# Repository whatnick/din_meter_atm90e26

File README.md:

# DIN Rail / PCI-X1 compatible ATM90E26 Metering Module

This is a 2 unit DIN-Rail size in width ATM90E26 based metering module with a host of nice features, designed for use with the DIN-Rail energy monitor modules system.

## Features

- PCI-X1 lower connector for interface with power and analog voltage/current signals.
- x2 ATM90E26 energy monitor ASICs and associated crystals, RC filter networks.
- Molex SPI bus and power pass-through upper connector.
- Dense single-sided PCB with 0402 passives.
- Test points and jumpers on the bottom to allow additional uses.

## Renders

**DIN Meter ATM90E26 Front**

**DIN Meter ATM90E26 Back**

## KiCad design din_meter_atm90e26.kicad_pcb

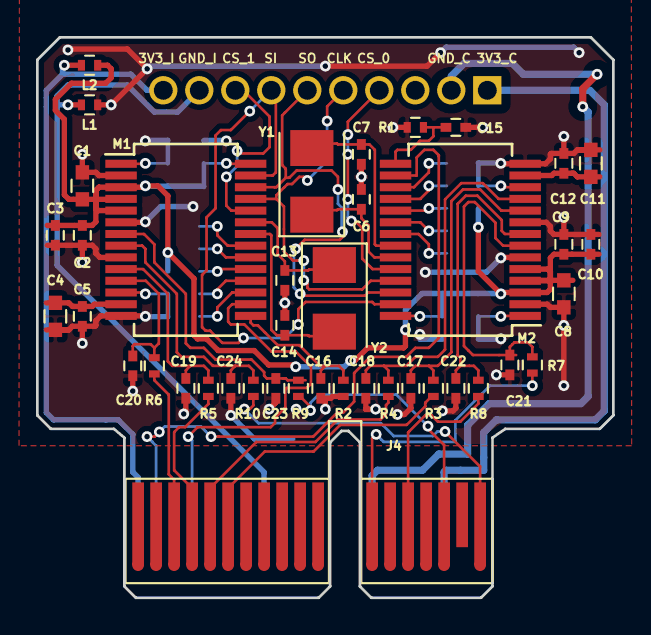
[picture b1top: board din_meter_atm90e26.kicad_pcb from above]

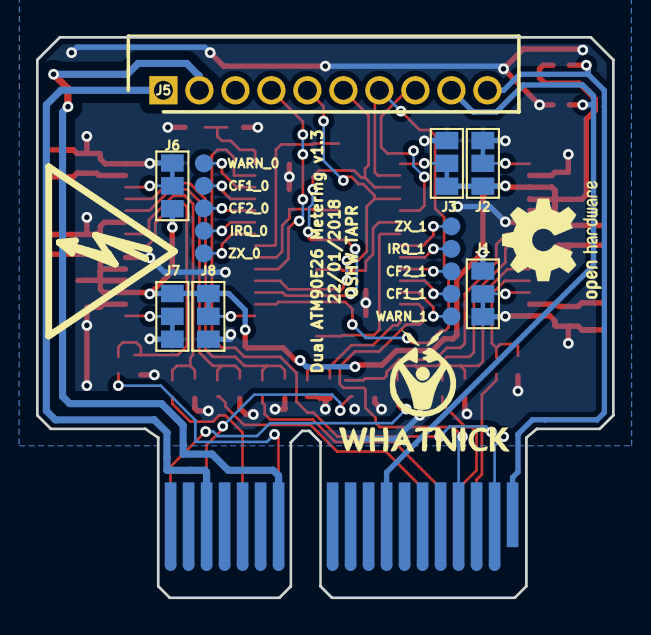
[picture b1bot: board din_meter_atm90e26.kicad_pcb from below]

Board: 2 copper layers, 32.0 x 31.1 mm, 61 parts (20 on the bottom side), 53 nets.

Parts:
C1, C4, C8, C11: 10u; C_0603
C2, C3, C5, C9, C10, C12: 100n; C_0402
C6, C7, C13, C14: 20p; C_0402
C15, C16, C17, C18, C19, C20, C21, C22, C23, C24: 33n; C_0402
CF1_0: CF1_0; Measurement_Point_Round-SMD-Pad_Small
CF1_1: CF1_1; Measurement_Point_Round-SMD-Pad_Small
CF2_0: CF2_0; Measurement_Point_Round-SMD-Pad_Small
CF2_1: CF2_1; Measurement_Point_Round-SMD-Pad_Small
G1: LOGO; Whatnick_logo
IRQ_0: IRQ_0; Measurement_Point_Round-SMD-Pad_Small
IRQ_1: IRQ_1; Measurement_Point_Round-SMD-Pad_Small
J1, J6: USEL; GS3
J2, J7: MMD1; GS3
J3, J8: MMD0; GS3
J4: CONN_02X18; PCI-EXPRESS
J5: CONN_01X10; SHDR10W60P200_1X10_2150X400X335P
L1: GND_SUP; L_0402
L2: 3V3_SUP; L_0402
LOGO1: Logo_Open_Hardware_Small; OSHW-Logo2_7.3x6mm_SilkScreen
M1, M2: ATM90E26_ATM90E26; SSOP-28_5.3x10.2mm_Pitch0.65mm
R1, R2, R3, R4, R5, R6, R7, R8, R9, R10: 1K; R_0402
SYM1: SYM_Flash_Small; Fsilk_HV
WARN_0: WARN_0; Measurement_Point_Round-SMD-Pad_Small
WARN_1: WARN_1; Measurement_Point_Round-SMD-Pad_Small
Y1, Y2: Crystal_Small; Crystal_SMD_5032-2pin_5.0x3.2mm
ZX_0: ZX_0; Measurement_Point_Round-SMD-Pad_Small
ZX_1: ZX_1; Measurement_Point_Round-SMD-Pad_Small

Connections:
3V3_CPU: J4.A16, J5.1
3V3_ISO: J4.A1, J5.10, L2.1
+3V3: C1.1, C2.2, C3.1, C8.1, C9.2, C10.1, J1.3, J2.3, J3.1, J6.3, J7.3, J8.1, L2.2, M1.3, M1.4, M1.5, M2.3, M2.4, M2.5
CF1_0: CF1_0.1, M2.18
CF1_1: CF1_1.1, M1.18
CF2_0: CF2_0.1, M2.19
CF2_1: CF2_1.1, M1.19
CLKIN_0: C7.2, M2.22, Y1.2
CLKIN_1: C14.2, M1.22, Y2.2
CLKOUT_0: C6.2, M2.23, Y1.1
CLKOUT_1: C13.2, M1.23, Y2.1
CS_0: J5.4, M2.24
CS_1: J5.8, M1.24
GNDD: C1.2, C2.1, C3.2, C4.2, C5.2, C6.1, C7.1, C8.2, C9.1, C10.2, C11.2, C12.2, C13.1, C14.1, C15.1, C16.1, C17.1, C18.1, C19.1, C20.1, C21.1, C22.1, C23.1, C24.1, J1.1, J2.1, J3.3, J6.1, J7.1, J8.3, L1.2, M1.2, M1.6, M1.9, M1.14, M2.2, M2.6, M2.9, M2.14, R1.2, R2.2
GND_CPU: J4.A12, J5.2
GND_ISO: J4.A8, J5.9, L1.1
I1N_0: C18.2, M2.11, R4.1
I1N_0_IN: J4.B5, R4.2
I1N_1: C20.2, M1.11, R6.1
I1N_1_IN: J4.B3, R6.2
I1P_0: C17.2, M2.10, R3.1
I1P_0_IN: J4.B6, R3.2
I1P_1: C19.2, M1.10, R5.1
I1P_1_IN: J4.B4, R5.2
I2N_0: C22.2, M2.8, R8.1
I2N_0_IN: J4.B14, R8.2
I2N_1: C24.2, M1.8, R10.1
I2N_1_IN: J4.B18, R10.2
I2P_0: C21.2, M2.7, R7.1
I2P_0_IN: J4.B12, R7.2
I2P_1: C23.2, M1.7, R9.1
I2P_1_IN: J4.B16, R9.2
IRQ_0: IRQ_0.1, M2.20
IRQ_1: IRQ_1.1, M1.20
unnamed: C4.1, C5.1, M1.13
unnamed: C11.1, C12.1, M2.13
unnamed: J1.2, M1.12
unnamed: J2.2, M1.1
unnamed: J3.2, M1.28
unnamed: J6.2, M2.12
unnamed: J7.2, M2.1
unnamed: J8.2, M2.28
SCLK: J5.5, M1.25, M2.25
SI/RX: J5.7, M1.27, M2.27
SO/TX: J5.6, M1.26, M2.26
VN_0: C15.2, M2.15, R1.1
VN_1: C16.2, M1.15, R2.1
VP_0: J4.A2, M2.16
VP_1: J4.A4, M1.16
WARN_0: M2.17, WARN_0.1
WARN_1: M1.17, WARN_1.1
ZX_0: M2.21, ZX_0.1
ZX_1: M1.21, ZX_1.1

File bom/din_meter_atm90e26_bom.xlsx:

References | manf# | Value | Footprint | Quantity
C6, C7, C13, C14 | GRM1555C1H200JA01D | 20p | C_0402 | 4
C15, C16, C17, C18, C19, C20, C21, C22, C23, C24 | GRM155B11A333KA01D | 33n | C_0402 | 10
C2, C3, C5, C9, C10, C12 | GRM155R71C104KA88D | 100n | C_0402 | 6
C1, C4, C8, C11 | GRM188R61A106KE69D | 10u | C_0603 | 4
R1, R2, R3, R4, R5, R6, R7, R8, R9, R10 | CRCW04021K00FKED | 1K | R_0402 | 10
L1 | BLM15AG100SN1D | GND_SUP | L_0402 | 1
L2 | BLM15AG100SN1D | 3V3_SUP | L_0402 | 1
Y1, Y2 | AA-8.192MAGE-T | Crystal_Small | Crystal_SMD_5032-2pin_5.0x3.2mm | 2
M1, M2 | ATM90E26-YU-B | ATM90E26_ATM90E26 | SSOP-28_5.3x10.2mm_Pitch0.65mm | 2
J5 | 52418-1010 | CONN_01X10 | SHDR10W60P200_1X10_2150X400X335P | 1

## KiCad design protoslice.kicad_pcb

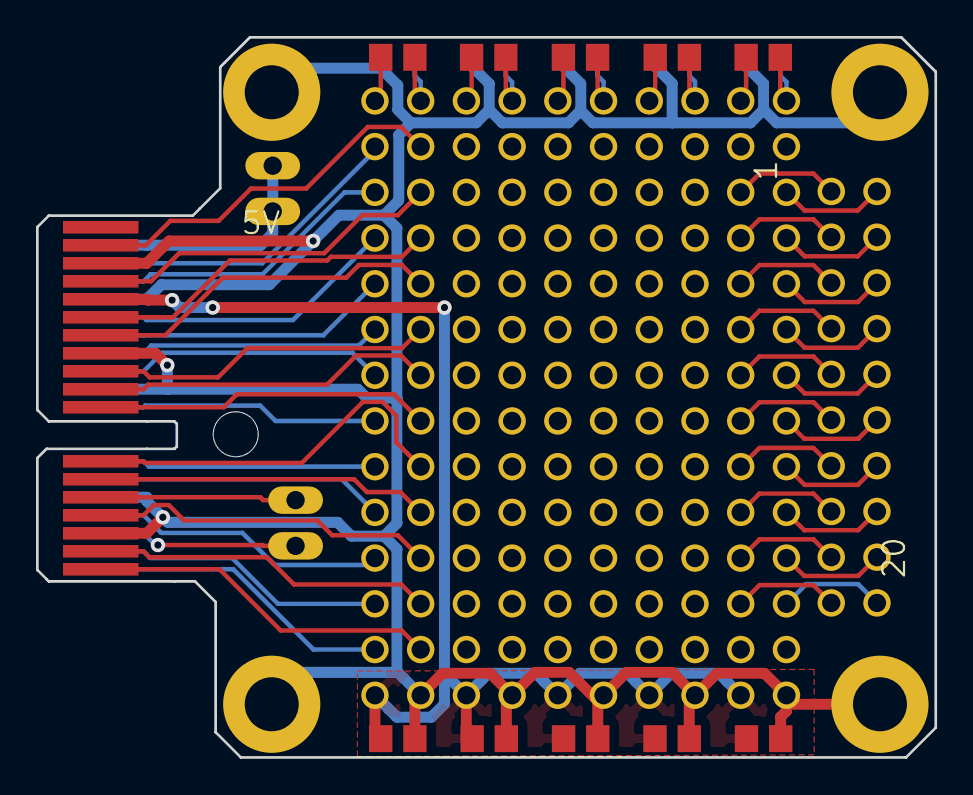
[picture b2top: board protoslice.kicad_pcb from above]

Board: 2 copper layers, 49.9 x 40.0 mm, 24 parts (0 on the bottom side), 59 nets.

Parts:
5V: 1X02
C1, C2, C3, C4, C5: C0805
JP1, JP2, JP3, JP4, JP5: 2X14
R1, R2, R3, R4, R5, R10, R11, R12, R13, R14: R0805
RST: 1X02
SV1: MA10-2
U$1: XSLICEXSLICE-SMALL; XSLICE-SMALL

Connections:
!RST: RST.1, U$1.A16
+3V3: C1.1, C2.1, C3.1, C4.1, C5.1, JP1.2, JP2.2, JP3.2, JP4.2, JP5.2, U$1.B5
+5V: 5V.1, 5V.2, U$1.A2
A3: JP1.26, U$1.A3
A4: JP1.24, U$1.A4
A6: JP1.22, U$1.A6
A7: JP1.20, U$1.A7
A8: JP1.18, U$1.A8
A9: JP1.16, U$1.A9
A11: JP1.14, U$1.A11
A12: JP1.12, U$1.A12
A13: JP1.10, U$1.A13
A15: JP1.8, U$1.A15
A17: JP1.6, U$1.A17
A18: JP1.4, U$1.A18
B2: JP1.25, U$1.B2
B4: JP1.23, U$1.B4
B6: JP1.21, U$1.B6
B7: JP1.19, U$1.B7
B9: JP1.17, U$1.B9
B10: JP1.15, U$1.B10
B11: JP1.13, U$1.B11
B12: JP1.11, U$1.B12
B13: JP1.9, U$1.B13
B15: JP1.7, U$1.B15
B17: JP1.5, U$1.B17
B18: JP1.3, U$1.B18
C1: JP5.24, SV1.1
C2: JP5.23, SV1.2
C3: JP5.22, SV1.3
C4: JP5.21, SV1.4
C5: JP5.20, SV1.5
C6: JP5.19, SV1.6
C7: JP5.18, SV1.7
C8: JP5.17, SV1.8
C9: JP5.16, SV1.9
C10: JP5.15, SV1.10
C11: JP5.14, SV1.11
C12: JP5.13, SV1.12
C13: JP5.12, SV1.13
C14: JP5.11, SV1.14
C15: JP5.10, SV1.15
C16: JP5.9, SV1.16
C17: JP5.8, SV1.17
C18: JP5.7, SV1.18
C19: JP5.6, SV1.19
C20: JP5.5, SV1.20
CLK: RST.2, U$1.B14
GND: C1.2, C2.2, C3.2, C4.2, C5.2, JP1.1, JP2.1, JP3.1, JP4.1, JP5.1, R10.1, R11.1, R12.1, R13.1, R14.1, U$1.A5, U$1.A10, U$1.A14, U$1.B3, U$1.B8, U$1.B16, U$1.H0, U$1.H1, U$1.H2, U$1.H3
unnamed: JP1.27, R1.1, R10.2
unnamed: JP1.28, R1.2
unnamed: JP2.27, R2.1, R11.2
unnamed: JP2.28, R2.2
unnamed: JP3.27, R3.1, R12.2
unnamed: JP3.28, R3.2
unnamed: JP4.27, R4.1, R13.2
unnamed: JP4.28, R4.2
unnamed: JP5.27, R5.1, R14.2
unnamed: JP5.28, R5.2

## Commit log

2017-10-07 Initial import
2017-10-10 Full import
2017-10-11 Initial place and route without PCI-E connector
2017-10-12 Renumber PCI-X
2017-10-13 Add labels to PCI-X
2017-10-15 v0.1 prepped for fab
2017-10-16 Update dimension
2017-10-16 Moved some tracks up to reduce exposure, updated screenshots
2017-10-16 Moved some tracks up to reduce exposure
2017-10-23 Update BOM
2017-11-20 Rerouted board from joslyn
2017-11-22 Add back logos and bump version
2017-11-22 New gerbers
2017-11-22 Update gerbers and dimensions
2017-11-22 Update gerbers
2017-12-07 Bump version and close jumpers using traces
2018-01-22 Open soldermask on gold fingers and bump version
2018-01-22 Fab layers to get dims
2018-01-22 added tapr licence on silk
2018-01-22 New gerbers with silk and vias on pads fixes
2018-01-22 Fix vias on pads
2018-02-24 Update BOM for use with Macrofab
2020-03-16 Migrate to KiCAD v5.0
2020-03-18 New gerbers and gitignore
2020-03-18 Remove ignored files
2020-03-18 Add excel BOM
2020-03-18 Update docs
2020-12-23 Remove protoslice stuff
2025-05-06 Upgrade to KiCAD 7.0

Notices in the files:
protoslice.kicad_pcb:
Copyright Alan Wood 2012
